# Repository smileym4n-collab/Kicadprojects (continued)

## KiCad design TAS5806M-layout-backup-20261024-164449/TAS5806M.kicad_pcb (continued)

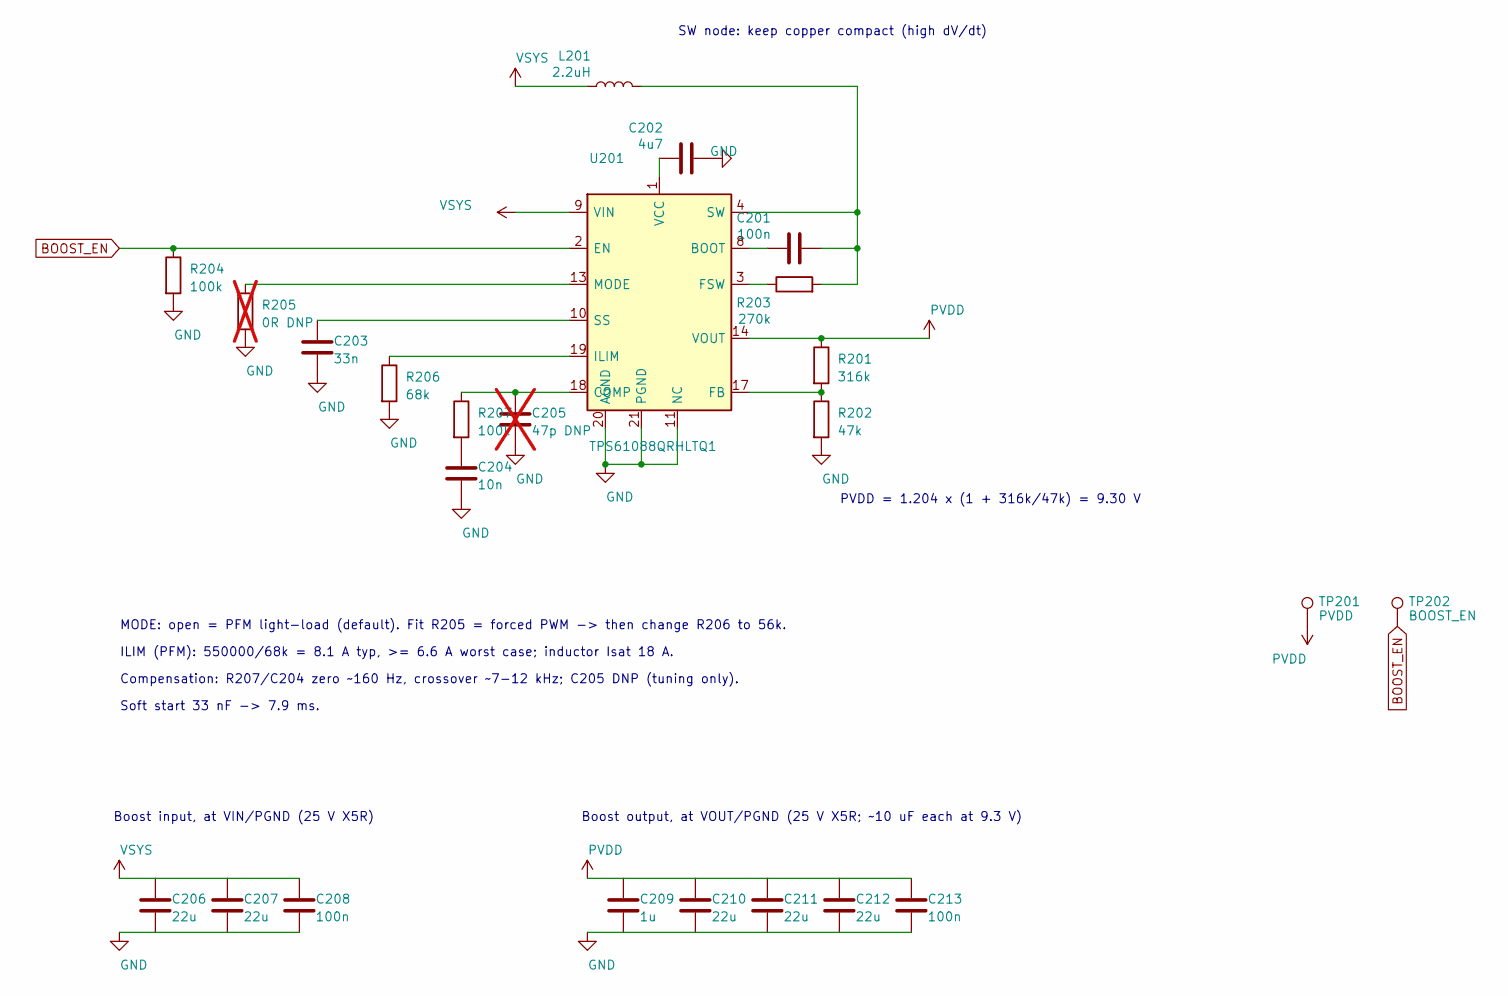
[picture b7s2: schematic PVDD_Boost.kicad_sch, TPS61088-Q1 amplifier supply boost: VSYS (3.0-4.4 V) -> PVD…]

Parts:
C201, C208, C213: 100n; C_0603_1608Metric_Pad1.08x0.95mm_HandSolder; MPN C0603C104M5RACTU
C202: 4u7; C_0805_2012Metric_Pad1.18x1.45mm_HandSolder; MPN CL21A475KAQNNNE
C203: 33n; C_0805_2012Metric_Pad1.18x1.45mm_HandSolder; MPN GRM2165C1H333JA01D
C204: 10n; C_0805_2012Metric_Pad1.18x1.45mm_HandSolder; MPN 0805N103J500CT
C205: 47p DNP; C_0603_1608Metric_Pad1.08x0.95mm_HandSolder; MPN GRM1885C1H470JA01D; not fitted
C206, C207, C210, C211, C212: 22u; C_1206_3216Metric_Pad1.33x1.80mm_HandSolder; MPN CL31A226KAHNNNE
C209: 1u; C_0805_2012Metric_Pad1.18x1.45mm_HandSolder; MPN CL21B105KAFNNNG
L201: 2.2uH; L_Bourns_SRP6060FA_BournsLayout; MPN SRP6060FA-2R2M
R201: 316k; R_0805_2012Metric; MPN 316K thick film 2012
R202: 47k; R_0805_2012Metric; MPN RMCF0805FT47K0
R203: 270k; R_0805_2012Metric; MPN 270K thick film 2012
R204: 100k; R_0805_2012Metric; MPN 100K thick film 2012
R205: 0R DNP; R_0805_2012Metric; MPN 0R link 2012; not fitted
R206: 68k; R_0805_2012Metric; MPN RC0805FR-0768KL
R207: 100k; R_0805_2012Metric; MPN 100K thin film 2012
TP201: PVDD; TestPoint_Pad_D1.5mm
TP202: BOOST_EN; TestPoint_Pad_D1.5mm
U201: TPS61088QRHLTQ1; Texas_VQFN-RHL-20_ThermalVias; MPN TPS61088QRHLTQ1

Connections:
BOOST_EN: R204.1, TP202.1 (1_1), U201.2 (EN); also elsewhere on the board
GND: C202.2, C203.2, C204.2, C205.2, C206.2, C207.2, C208.2, C209.2, C210.2, C211.2, C212.2, C213.2, R202.2, R204.2, R205.2, R206.2, U201.11 (NC), U201.12 (NC), U201.20 (AGND), U201.21 (PGND); also elsewhere on the board
unnamed: C201.2, L201.2, R203.2, U201.4 (SW), U201.5 (SW), U201.6 (SW), U201.7 (SW)
unnamed: C204.1, R207.2
unnamed: C201.1, U201.8 (BOOT)
unnamed: C205.1, R207.1, U201.18 (COMP)
unnamed: R201.2, R202.1, U201.17 (FB)
unnamed: R203.1, U201.3 (FSW)
unnamed: R206.1, U201.19 (ILIM)
unnamed: R205.1, U201.13 (MODE)
unnamed: C203.1, U201.10 (SS)
unnamed: C202.1, U201.1 (VCC)
PVDD: C209.1, C210.1, C211.1, C212.1, C213.1, R201.1, TP201.1 (1_1), U201.14 (VOUT), U201.15 (VOUT), U201.16 (VOUT); also elsewhere on the board
VSYS: C206.1, C207.1, C208.1, L201.1, U201.9 (VIN); also elsewhere on the board

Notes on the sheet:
ILIM (PFM): 550000/68k = 8.1 A typ, >= 6.6 A worst case; inductor Isat 18 A.
PVDD = 1.204 x (1 + 316k/47k) = 9.30 V
SW node: keep copper compact (high dV/dt)
MODE: open = PFM light-load (default). Fit R205 = forced PWM -> then change R206 to 56k.
Soft start 33 nF -> 7.9 ms.
Boost output, at VOUT/PGND (25 V X5R; ~10 uF each at 9.3 V)
Compensation: R207/C204 zero ~160 Hz, crossover ~7-12 kHz; C205 DNP (tuning only).
Boost input, at VIN/PGND (25 V X5R)

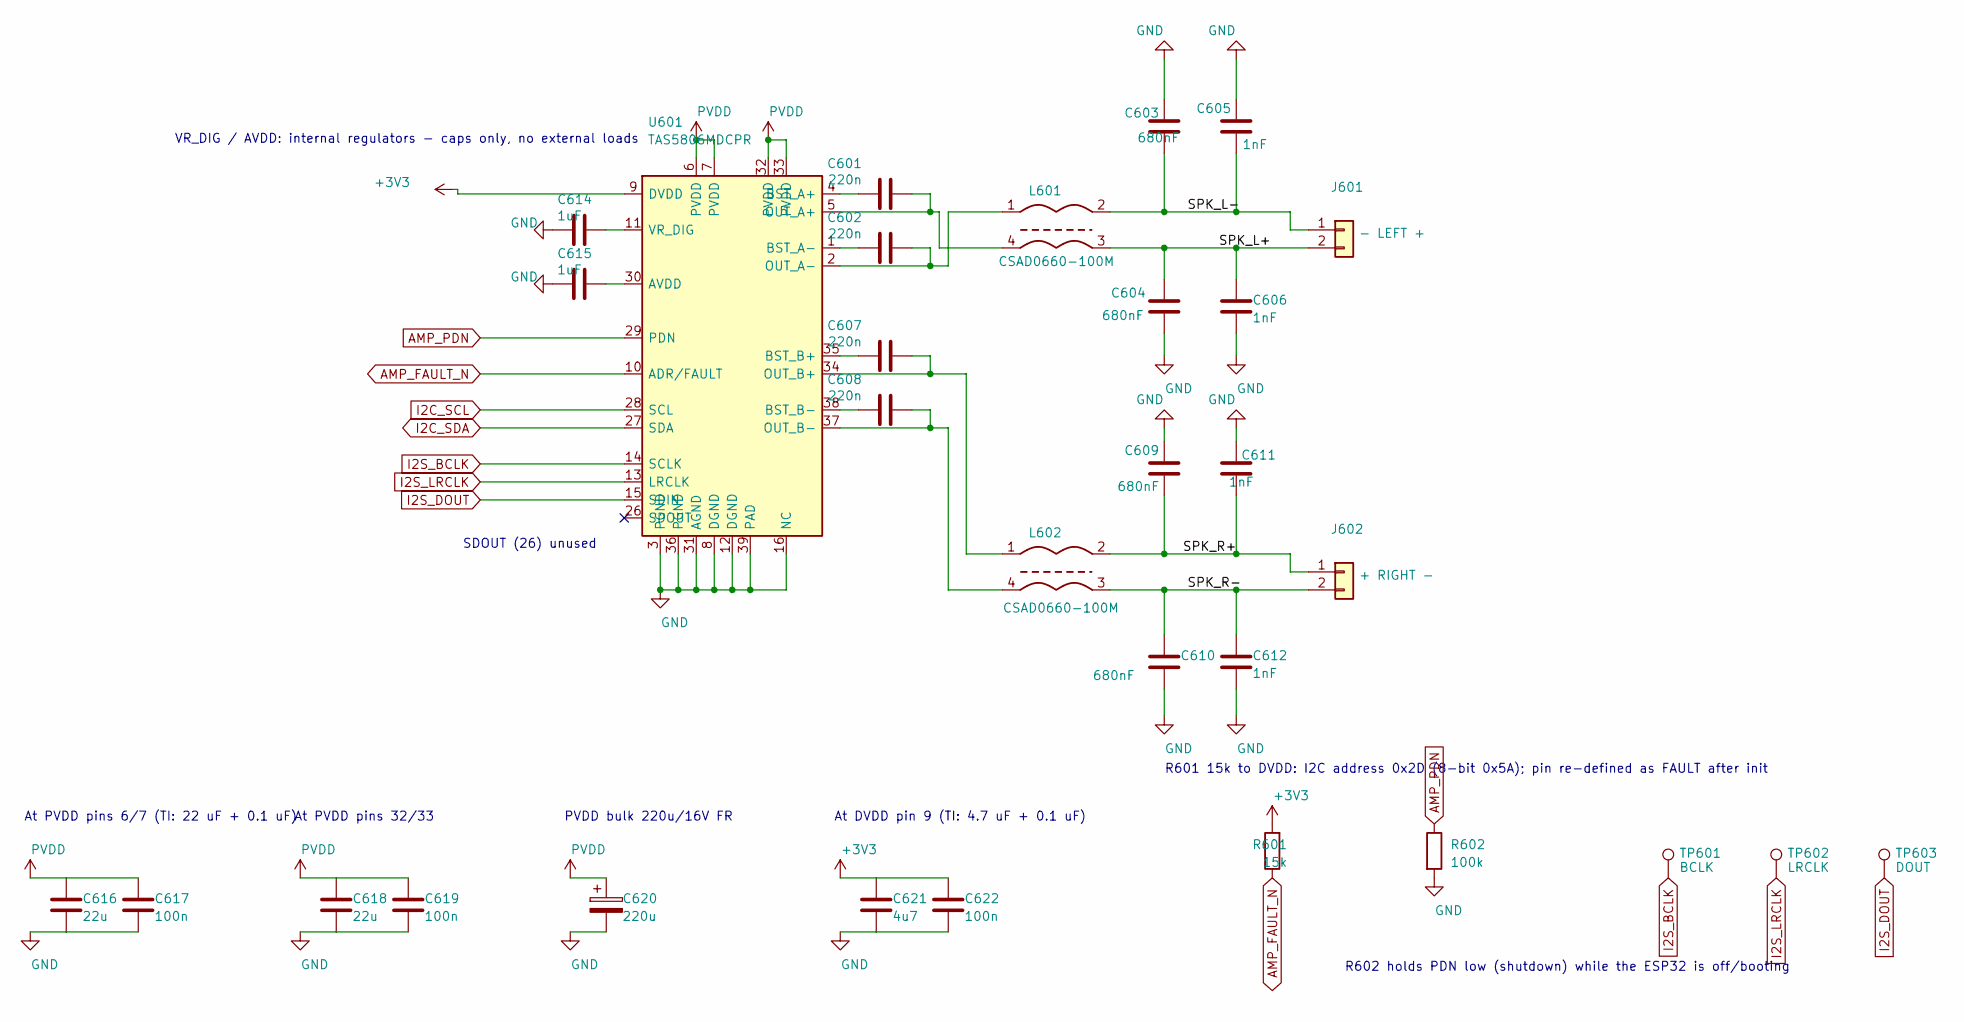
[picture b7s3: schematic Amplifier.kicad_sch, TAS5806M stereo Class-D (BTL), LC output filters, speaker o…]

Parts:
C601, C602, C607, C608: 220n; C_0805_2012Metric_Pad1.18x1.45mm_HandSolder; MPN CL21B224KAFNNNE
C603, C604, C609, C610: 680nF; C_Rect_L7.2mm_W4.5mm_P5.00mm_FKS2_FKP2_MKS2_MKP2; MPN R82DC3680Z360J
C605, C606, C611, C612: 1nF; C_0805_2012Metric_Pad1.18x1.45mm_HandSolder; MPN MC0805N102J500CT
C614, C615: 1uF; C_0805_2012Metric_Pad1.18x1.45mm_HandSolder; MPN CL21B105KAFNNNG
C616, C618: 22u; C_1206_3216Metric_Pad1.33x1.80mm_HandSolder; MPN CL31A226KAHNNNE
C617, C619, C622: 100n; C_0603_1608Metric_Pad1.08x0.95mm_HandSolder; MPN C0603C104M5RACTU
C620: 220u; CP_Radial_D6.3mm_P2.50mm; MPN EEUFR1C221B
C621: 4u7; C_0805_2012Metric_Pad1.18x1.45mm_HandSolder; MPN CL21A475KAQNNNE
J601: - LEFT +; Molex_KK-254_AE-6410-02A_1x02_P2.54mm_Vertical; MPN MC34629 (+ housing MC34481)
J602: + RIGHT -; Molex_KK-254_AE-6410-02A_1x02_P2.54mm_Vertical; MPN MC34629 (+ housing MC34481)
L601, L602: CSAD0660-100M; MPN CSAD0660-100M
R601: 15k; R_0805_2012Metric; MPN 15K thin film 2012
R602: 100k; R_0805_2012Metric; MPN 100K thick film 2012
TP601: BCLK; TestPoint_Pad_D1.5mm
TP602: LRCLK; TestPoint_Pad_D1.5mm
TP603: DOUT; TestPoint_Pad_D1.5mm
U601: TAS5806MDCPR; HTSSOP-38-1EP_4.4x9.7mm_P0.5mm_EP2.74x4.75mm_ThermalVias; MPN TAS5806MDCPR

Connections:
+3V3: C621.1, C622.1, R601.2, U601.9 (DVDD); also elsewhere on the board
/AMPLIFIER/SPK_L+: C604.1, C606.1, J601.2, L601.3
/AMPLIFIER/SPK_L-: C603.1, C605.1, J601.1, L601.2
/AMPLIFIER/SPK_R+: C609.1, C611.1, J602.1, L602.2
/AMPLIFIER/SPK_R-: C610.1, C612.1, J602.2, L602.3
AMP_FAULT_N: R601.1, U601.10 (ADR/FAULT); also elsewhere on the board
AMP_PDN: R602.1, U601.29 (PDN); also elsewhere on the board
GND: C603.2, C604.2, C605.2, C606.2, C609.2, C610.2, C611.2, C612.2, C614.2, C615.2, C616.2, C617.2, C618.2, C619.2, C620.2, C621.2, C622.2, R602.2, U601.3 (PGND), U601.8 (DGND), U601.12 (DGND), U601.16 (NC), U601.17 (NC), U601.18 (NC), U601.19 (NC), U601.20 (NC), U601.21 (NC), U601.22 (NC), U601.23 (NC), U601.24 (NC), U601.25 (NC), U601.31 (AGND), U601.36 (PGND), U601.39 (PAD); also elsewhere on the board
I2C_SCL: U601.28 (SCL); also elsewhere on the board
I2C_SDA: U601.27 (SDA); also elsewhere on the board
I2S_BCLK: TP601.1 (1_1), U601.14 (SCLK); also elsewhere on the board
I2S_DOUT: TP603.1 (1_1), U601.15 (SDIN); also elsewhere on the board
I2S_LRCLK: TP602.1 (1_1), U601.13 (LRCLK); also elsewhere on the board
unnamed: C615.1, U601.30 (AVDD)
unnamed: C601.1, U601.4 (BST_A+)
unnamed: C602.1, U601.1 (BST_A-)
unnamed: C607.1, U601.35 (BST_B+)
unnamed: C608.1, U601.38 (BST_B-)
unnamed: C601.2, L601.4, U601.5 (OUT_A+)
unnamed: C602.2, L601.1, U601.2 (OUT_A-)
unnamed: C607.2, L602.1, U601.34 (OUT_B+)
unnamed: C608.2, L602.4, U601.37 (OUT_B-)
unnamed: C614.1, U601.11 (VR_DIG)
PVDD: C616.1, C617.1, C618.1, C619.1, C620.1, U601.6 (PVDD), U601.7 (PVDD), U601.32 (PVDD), U601.33 (PVDD); also elsewhere on the board

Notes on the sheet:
R601 15k to DVDD: I2C address 0x2D (8-bit 0x5A); pin re-defined as FAULT after init
At PVDD pins 32/33
VR_DIG / AVDD: internal regulators - caps only, no external loads
PVDD bulk 220u/16V FR
At PVDD pins 6/7 (TI: 22 uF + 0.1 uF)
R602 holds PDN low (shutdown) while the ESP32 is off/booting
SDOUT (26) unused
At DVDD pin 9 (TI: 4.7 uF + 0.1 uF)

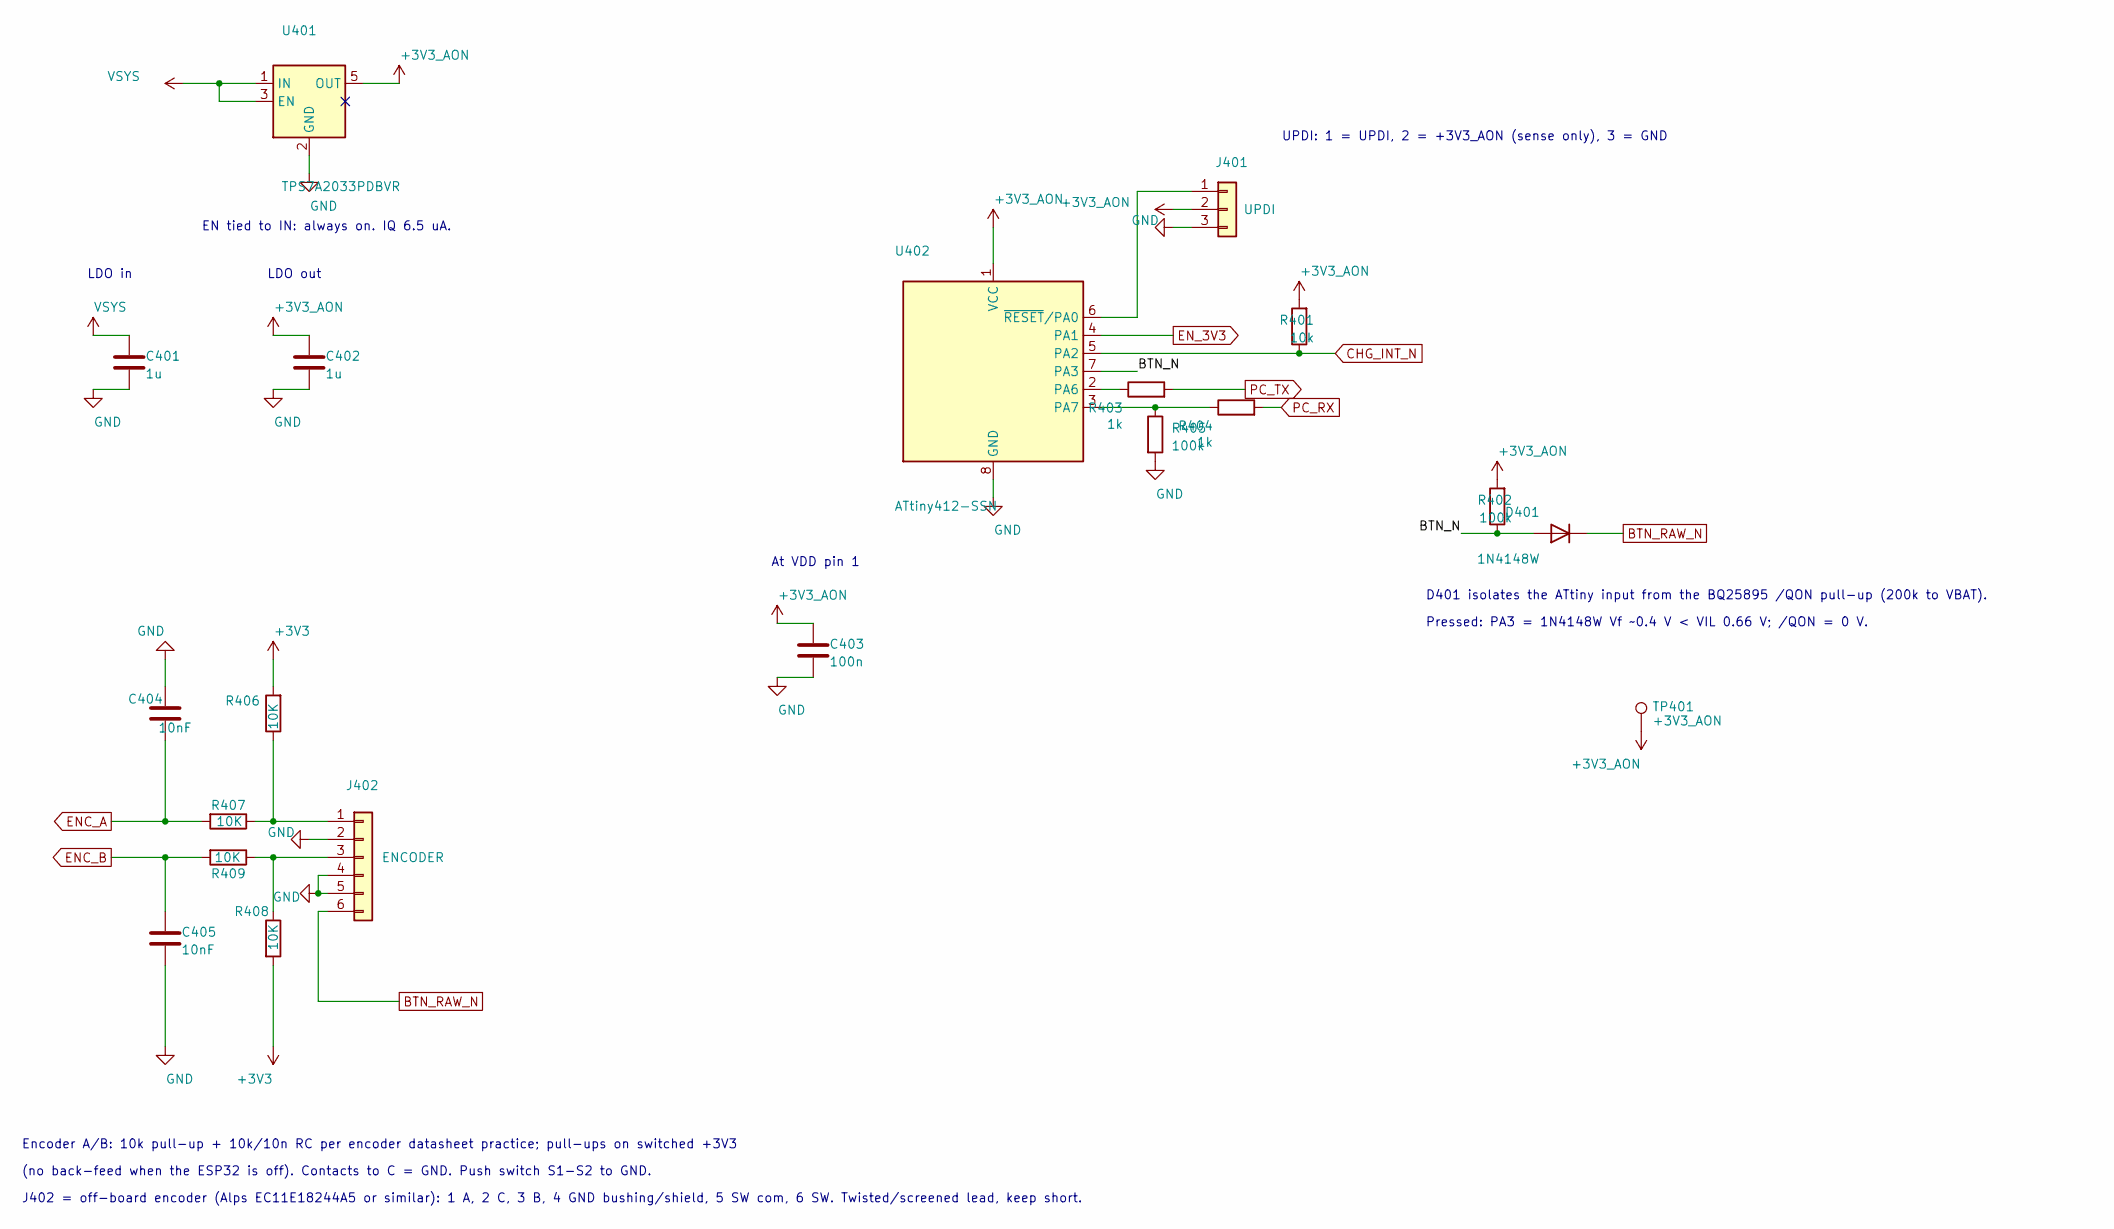
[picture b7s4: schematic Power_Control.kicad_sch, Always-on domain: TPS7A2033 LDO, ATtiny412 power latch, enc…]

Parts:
C401, C402: 1u; C_0805_2012Metric_Pad1.18x1.45mm_HandSolder; MPN CL21B105KAFNNNG
C403: 100n; C_0603_1608Metric_Pad1.08x0.95mm_HandSolder; MPN C0603C104M5RACTU
C404, C405: 10nF; C_0805_2012Metric_Pad1.18x1.45mm_HandSolder; MPN 0805N103J500CT
D401: 1N4148W; D_SOD-123; MPN 1N4148W
J401: UPDI; Molex_KK-254_AE-6410-03A_1x03_P2.54mm_Vertical; MPN MC34631 (+ housing MC34483)
J402: ENCODER; Molex_KK-254_AE-6410-06A_1x06_P2.54mm_Vertical; MPN MC34635 (+ housing MC34487)
R401: 10k; R_0805_2012Metric; MPN RK73B2ATTD103J
R402, R405: 100k; R_0805_2012Metric; MPN 100K thick film 2012
R403, R404: 1k; R_0805_2012Metric; MPN 1K thick film 2012
R406, R407, R408, R409: 10K; R_0805_2012Metric; MPN RK73B2ATTD103J
TP401: +3V3_AON; TestPoint_Pad_D1.5mm
U401: TPS7A2033PDBVR; SOT-23-5; MPN TPS7A2033PDBVR
U402: ATtiny412-SSN; SOIC-8_3.9x4.9mm_P1.27mm; MPN ATTINY412-SSN

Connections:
+3V3: R406.2, R408.2; also elsewhere on the board
+3V3_AON: C402.1, C403.1, J401.2, R401.2, R402.2, TP401.1 (1_1), U401.5 (OUT), U402.1 (VCC)
/POWER_CTRL/BTN_N: D401.2 (A), R402.1, U402.7 (PA3)
BTN_RAW_N: D401.1 (K), J402.6; also elsewhere on the board
CHG_INT_N: R401.1, U402.5 (PA2); also elsewhere on the board
ENC_A: C404.1, R407.2; also elsewhere on the board
ENC_B: C405.1, R409.2; also elsewhere on the board
EN_3V3: U402.4 (PA1); also elsewhere on the board
GND: C401.2, C402.2, C403.2, C404.2, C405.2, J401.3, J402.2, J402.4, J402.5, R405.2, U401.2 (GND), U402.8 (GND); also elsewhere on the board
unnamed: J401.1, U402.6 (~RESET/PA0)
unnamed: J402.1, R406.1, R407.1
unnamed: J402.3, R408.1, R409.1
unnamed: R403.1, U402.2 (PA6)
unnamed: R404.1, R405.1, U402.3 (PA7)
PC_RX: R404.2; also elsewhere on the board
PC_TX: R403.2; also elsewhere on the board
VSYS: C401.1, U401.1 (IN), U401.3 (EN); also elsewhere on the board

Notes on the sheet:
D401 isolates the ATtiny input from the BQ25895 /QON pull-up (200k to VBAT).
EN tied to IN: always on. IQ 6.5 uA.
Encoder A/B: 10k pull-up + 10k/10n RC per encoder datasheet practice; pull-ups on switched +3V3
UPDI: 1 = UPDI, 2 = +3V3_AON (sense only), 3 = GND
LDO in
At VDD pin 1
LDO out
J402 = off-board encoder (Alps EC11E18244A5 or similar): 1 A, 2 C, 3 B, 4 GND bushing/shield, 5 SW com, 6 SW. Twisted/screened lead, keep short.
Pressed: PA3 = 1N4148W Vf ~0.4 V < VIL 0.66 V; /QON = 0 V.
(no back-feed when the ESP32 is off). Contacts to C = GND. Push switch S1-S2 to GND.

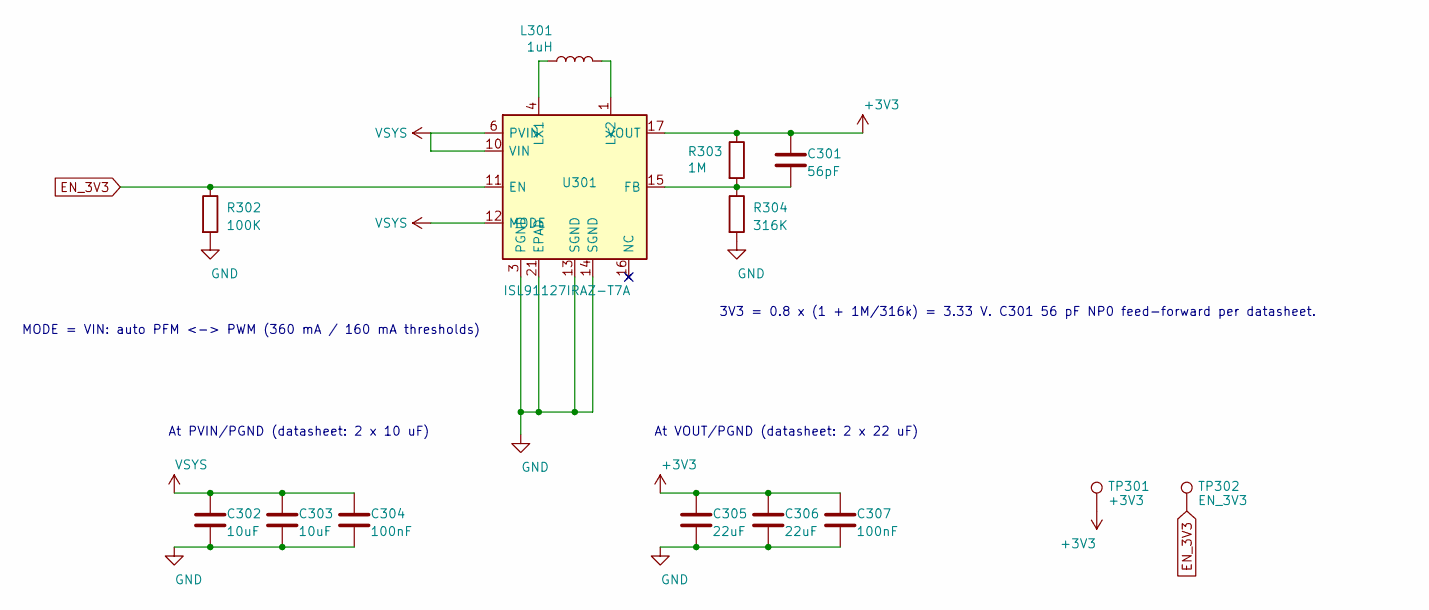
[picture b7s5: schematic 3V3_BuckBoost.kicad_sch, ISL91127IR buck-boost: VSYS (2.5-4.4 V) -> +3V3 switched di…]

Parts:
C301: 56pF; C_0603_1608Metric_Pad1.08x0.95mm_HandSolder; MPN GRM1885C1H560JA01D
C302, C303: 10uF; C_1206_3216Metric_Pad1.33x1.80mm_HandSolder; MPN TMK316B7106KL-TD
C304, C307: 100nF; C_0603_1608Metric_Pad1.08x0.95mm_HandSolder; MPN C0603C104M5RACTU
C305, C306: 22uF; C_0805_2012Metric_Pad1.18x1.45mm_HandSolder; MPN (inventory id 339, MPN not recorded)
L301: 1uH; L_Wuerth_MAPI-4020; MPN 74438356010
R302: 100K; R_0805_2012Metric; MPN 100K thick film 2012
R303: 1M; R_0805_2012Metric; MPN 1M thin film 2012
R304: 316K; R_0805_2012Metric; MPN 316K thick film 2012
TP301: +3V3; TestPoint_Pad_D1.5mm
TP302: EN_3V3; TestPoint_Pad_D1.5mm
U301: ISL91127IRAZ-T7A; QFN-20-1EP_4x4mm_P0.5mm_EP2.7x2.7mm_ThermalVias; MPN ISL91127IRAZ-T7A

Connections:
+3V3: C301.1, C305.1, C306.1, C307.1, R303.1, TP301.1 (1_1), U301.17 (VOUT), U301.18 (VOUT), U301.19 (VOUT), U301.20 (VOUT); also elsewhere on the board
EN_3V3: R302.1, TP302.1 (1_1), U301.11 (EN); also elsewhere on the board
GND: C302.2, C303.2, C304.2, C305.2, C306.2, C307.2, R302.2, R304.2, U301.3 (PGND), U301.13 (SGND), U301.14 (SGND), U301.21 (EPAD); also elsewhere on the board
unnamed: L301.1, U301.4 (LX1), U301.5 (LX1)
unnamed: L301.2, U301.1 (LX2), U301.2 (LX2)
unnamed: C301.2, R303.2, R304.1, U301.15 (FB)
VSYS: C302.1, C303.1, C304.1, U301.6 (PVIN), U301.7 (PVIN), U301.8 (PVIN), U301.9 (PVIN), U301.10 (VIN), U301.12 (MODE); also elsewhere on the board

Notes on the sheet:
At PVIN/PGND (datasheet: 2 x 10 uF)
At VOUT/PGND (datasheet: 2 x 22 uF)
MODE = VIN: auto PFM <-> PWM (360 mA / 160 mA thresholds)
3V3 = 0.8 x (1 + 1M/316k) = 3.33 V. C301 56 pF NP0 feed-forward per datasheet.

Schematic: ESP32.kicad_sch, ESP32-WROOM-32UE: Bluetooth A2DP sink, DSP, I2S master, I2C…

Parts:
C501: 1u; C_0805_2012Metric_Pad1.18x1.45mm_HandSolder; MPN CL21B105KAFNNNG
C502: 22u; C_0805_2012Metric_Pad1.18x1.45mm_HandSolder; MPN (inventory id 339, MPN not recorded)
C503: 10u; C_0805_2012Metric_Pad1.18x1.45mm_HandSolder; MPN CL21A106KOQNNNF
C504: 100n; C_0603_1608Metric_Pad1.08x0.95mm_HandSolder; MPN C0603C104M5RACTU
D501: GREEN; LED_0805_2012Metric; MPN KP-2012LSGC
J501: ESP PROG; PinHeader_1x06_P2.54mm_Vertical; MPN MC34635
R501, R506: 10k; R_0805_2012Metric; MPN RK73B2ATTD103J
R502, R503, R504: 22R; R_0603_1608Metric; MPN RK73B1JTTD220J
R505: 1k; R_0805_2012Metric; MPN 1K thick film 2012
R507, R508: 4k7; R_0805_2012Metric; MPN RMCF0805FT4K70
SW501: RESET; TS026650BK100SCRD; MPN TS02-66-50-BK-100-SCR-D
SW502: BOOT; TS026650BK100SCRD; MPN TS02-66-50-BK-100-SCR-D
TP501: IO14; TestPoint_Pad_D1.5mm
TP502: IO17; TestPoint_Pad_D1.5mm
TP503: IO19; TestPoint_Pad_D1.5mm
U501: ESP32-WROOM-32UE-N8R2; ESP32WROOM32UEN8R2; MPN ESP32-WROOM-32UE-N8R2

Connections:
+3V3: C502.1, C503.1, C504.1, J501.2, R501.2, R506.2, R507.2, R508.2, U501.2 (3V3); also elsewhere on the board
/ESP32/ESP_EN: C501.1, J501.5, R501.1, SW501.1 (NO), SW501.2 (NO), U501.3 (EN)
/ESP32/ESP_IO0: J501.6, SW502.1 (NO), SW502.2 (NO), U501.25 (IO0)
/ESP32/ESP_IO16: R506.1, U501.27 (IO16)
/ESP32/ESP_RXD0: J501.4, U501.34 (RXD0)
/ESP32/ESP_TXD0: J501.3, U501.35 (TXD0)
AMP_FAULT_N: U501.30 (IO18); also elsewhere on the board
AMP_PDN: U501.37 (IO23); also elsewhere on the board
BOOST_EN: U501.26 (IO4); also elsewhere on the board
CC1_SENSE: U501.4 (SENSOR_VP); also elsewhere on the board
CC2_SENSE: U501.5 (SENSOR_VN); also elsewhere on the board
ENC_A: U501.6 (IO34); also elsewhere on the board
ENC_B: U501.7 (IO35); also elsewhere on the board
GND: C501.2, C502.2, C503.2, C504.2, D501.1 (K), J501.1, SW501.3 (COM), SW501.4 (COM), SW502.3 (COM), SW502.4 (COM), U501.1 (GND_1), U501.15 (GND_2), U501.38 (GND_3), U501.39 (GND_4), U501.40 (GND_5), U501.41 (GND_6), U501.42 (GND_7), U501.43 (GND_8), U501.44 (GND_9), U501.45 (GND_10), U501.46 (GND_11), U501.47 (GND_12); also elsewhere on the board
I2C_SCL: R508.1, U501.36 (IO22); also elsewhere on the board
I2C_SDA: R507.1, U501.33 (IO21); also elsewhere on the board
I2S_BCLK: R503.2; also elsewhere on the board
I2S_DOUT: R504.2; also elsewhere on the board
I2S_LRCLK: R502.2; also elsewhere on the board
unnamed: D501.2 (A), R505.2
unnamed: R505.1, U501.16 (IO13)
unnamed: TP501.1 (1_1), U501.13 (IO14)
unnamed: TP502.1 (1_1), U501.28 (IO17)
unnamed: TP503.1 (1_1), U501.31 (IO19)
unnamed: R502.1, U501.10 (IO25)
unnamed: R503.1, U501.11 (IO26)
unnamed: R504.1, U501.12 (IO27)
PC_RX: U501.9 (IO33); also elsewhere on the board
PC_TX: U501.8 (IO32); also elsewhere on the board

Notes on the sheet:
disconnected (ISL91127 off: its 120R output discharge draws ~27 mA - acceptable).
ANTENNA: WROOM-32UE uses an external U.FL antenna - route the coax away from PVDD/boost/Class-D
J501: 1 GND, 2 +3V3, 3 TXD0 (ESP out), 4 RXD0 (ESP in), 5 EN, 6 IO0.
EN RC 10k / 1u per Espressif (power-up delay)
Pin 2 may power the 3V3 rail from a 3.3 V adapter for bench flashing with the battery
At module pin 2 (Espressif: 22 uF + 100 nF; +10 uF for RF bursts)
IO16 = PSRAM CS on N8R2: 10k pull-up (Espressif)
Bus is unpowered (0 V) when +3V3 is off - BQ25895 SCL/SDA tolerate this.
17-22: module NC. IO15/IO2/IO12: strapping, unused.
outputs; no PCB keep-out is required for the UE variant (datasheet sec. 3.1).
22R source terminations at the ESP32 pins (I2S lines to TAS5806M)
IO0 has an internal pull-up; hold BOOT while pulsing RESET for the ROM loader.
I2C pull-ups 4k7 to +3V3 (400 kHz, BQ25895 + TAS5806M).

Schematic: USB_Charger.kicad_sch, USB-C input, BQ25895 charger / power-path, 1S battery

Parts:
C101, C102: 10n; C_0805_2012Metric_Pad1.18x1.45mm_HandSolder; MPN 0805N103J500CT
C103: 10u; C_1206_3216Metric_Pad1.33x1.80mm_HandSolder; MPN CL31A106KBHNNNE
C104: 47n; C_0603_1608Metric_Pad1.08x0.95mm_HandSolder; MPN GRM188R71H473KA61D
C105: 1u; C_0805_2012Metric_Pad1.18x1.45mm_HandSolder; MPN CL21B105KAFNNNG
C106, C107: 22u; C_1206_3216Metric_Pad1.33x1.80mm_HandSolder; MPN CL31A226KAHNNNE
C108, C111: 100n; C_0603_1608Metric_Pad1.08x0.95mm_HandSolder; MPN C0603C104M5RACTU
C109: 10u; C_1206_3216Metric_Pad1.33x1.80mm_HandSolder; MPN TMK316B7106KL-TD
C110: 4u7; C_0805_2012Metric_Pad1.18x1.45mm_HandSolder; MPN CL21A475KAQNNNE
D101: TVS1400DRVR; WSON-6-1EP_2x2mm_P0.65mm_EP1x1.6mm; MPN TVS1400DRVR
D102: RED; LED_0805_2012Metric; MPN KP-2012EC
F101: 8A; Fuse_Littelfuse-NANO2-451_453; MPN 0451008.MRL
J101: USB4105-GF-A; USB_C_Receptacle_GCT_USB4105-xx-A_16P_TopMnt_Horizontal; MPN USB4105-GF-A
J102: BATTERY 1S; Molex_KK-396_A-41791-0002_1x02_P3.96mm_Vertical; MPN 09-65-2028 (41791-0002)
J103: BATT NTC 10k; Molex_KK-254_AE-6410-02A_1x02_P2.54mm_Vertical; MPN MC34629 (+ housing MC34481)
L101: 1uH; L_Wuerth_MAPI-4020; MPN 74438356010
R101: 150R; R_0805_2012Metric; MPN RC0805FR-07150RL
R102, R104: 5K1; R_0805_2012Metric; MPN RC0805FR-135K1L
R103, R105: 100k; R_0805_2012Metric; MPN 100K thick film 2012
R106: 1k5; R_0603_1608Metric; MPN 1K5 thick film 1608
R107: 5k23; R_0805_2012Metric; MPN RMCF0805FT5K23
R108: 30k; R_0805_2012Metric; MPN RMCF0805FT30K0
RT101: 10k B3435 DNP; R_0603_1608Metric; MPN NCU18XH103F60RB; not fitted
TP101: VBUS; TestPoint_Pad_D1.5mm
TP102: VSYS; TestPoint_Pad_D1.5mm
TP103: VBAT; TestPoint_Pad_D1.5mm
TP104: GND; TestPoint_Pad_D1.5mm
U101: BQ25895RTWR; Texas_RTW_WQFN-24-1EP_4x4mm_P0.5mm_EP2.7x2.7mm_ThermalVias; MPN BQ25895RTWR
U102: TPD2E2U06DCKR; SOT-323_SC-70; MPN TPD2E2U06DCKR

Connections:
/USB_CHARGER/CC1: J101.A5 (CC1), R102.1, R103.1
/USB_CHARGER/CC2: J101.B5 (CC2), R104.1, R105.1
/USB_CHARGER/USB_DN: J101.A7 (D-), J101.B7 (D-), U101.3 (D-), U102.2 (IO2)
/USB_CHARGER/USB_DP: J101.A6 (D+), J101.B6 (D+), U101.2 (D+), U102.1 (IO1)
BTN_RAW_N: U101.12 (~QON); also elsewhere on the board
CC1_SENSE: C101.1, R103.2; also elsewhere on the board
CC2_SENSE: C102.1, R105.2; also elsewhere on the board
CHG_INT_N: U101.7 (~INT); also elsewhere on the board
GND: C101.2, C102.2, C103.2, C105.2, C106.2, C107.2, C108.2, C109.2, C110.2, C111.2, D101.1 (GND), D101.2 (GND), D101.3 (GND), D101.7 (GND), J101.A1 (GND), J101.A12 (GND), J101.B1 (GND), J101.B12 (GND), J101.SH (SHIELD), J102.2, J103.2, R101.2, R102.2, R104.2, R108.2, RT101.2, TP104.1 (1_1), U101.8 (OTG), U101.9 (~CE), U101.17 (PGND), U101.18 (PGND), U101.25 (PGND), U102.3 (GND); also elsewhere on the board
I2C_SCL: U101.5 (SCL); also elsewhere on the board
I2C_SDA: U101.6 (SDA); also elsewhere on the board
unnamed: C104.1, L101.1, U101.19 (SW), U101.20 (SW)
unnamed: D102.2 (A), R106.1
unnamed: D102.1 (K), U101.4 (STAT)
unnamed: F101.1, J102.1
unnamed: J103.1, R107.2, R108.1, RT101.1, U101.11 (TS)
unnamed: C104.2, U101.21 (BTST)
unnamed: R101.1, U101.10 (ILIM)
unnamed: C103.1, U101.23 (PMID)
unnamed: C110.1, R107.1, U101.22 (REGN)
VBAT: C109.1, C111.1, F101.2, TP103.1 (1_1), U101.13 (BAT), U101.14 (BAT)
VBUS: C105.1, D101.4 (IN), D101.5 (IN), D101.6 (IN), J101.A4 (VBUS), J101.A9 (VBUS), J101.B4 (VBUS), J101.B9 (VBUS), TP101.1 (1_1), U101.1 (VBUS)
VSYS: C106.1, C107.1, C108.1, L101.2, R106.2, TP102.1 (1_1), U101.15 (SYS), U101.16 (SYS); also elsewhere on the board

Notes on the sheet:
Back-feed into unpowered ESP32 <= 15 uA (accepted).
CC sense: 100k series + 10n reservoir at ESP32 ADC1 (place C at ESP32).
At SYS pins 15/16 (>= 20 uF eff.)
OTG pin = GND: boost (OTG) mode can never start
Cell has internal protection (OV/UV/OC); F101 8 A and BQ25895 9 A BATFET OCP back it up.
18.4 V clamp < 22 V BQ25895 VBUS abs max
TVS1400: 14 V standoff (allows HVDCP 9/12 V),
No NTC fitted -> TS reads 85% REGN = COLD -> charging suspended (safe default).
BATTERY: pin 1 = BAT+ (red), pin 2 = BAT- (black). Polarised KK-396.
USB-C sink: Rd = 5.1k on CC1/CC2 (no PD). Shell tied to GND.
CHARGE LED: on = charging, 1 Hz blink = fault
D+/D- go only to BQ25895 BC1.2 detection.
At VBUS pin 1
NTC: 10k B3435 (103AT) bonded to the cell on J103, OR fit RT101 on board - never both.
No reverse-polarity FET fitted (see design notes): CHECK POLARITY BEFORE MATING.
At BAT pins 13/14
ILIM 150R: USB input ceiling 2.37 A typ

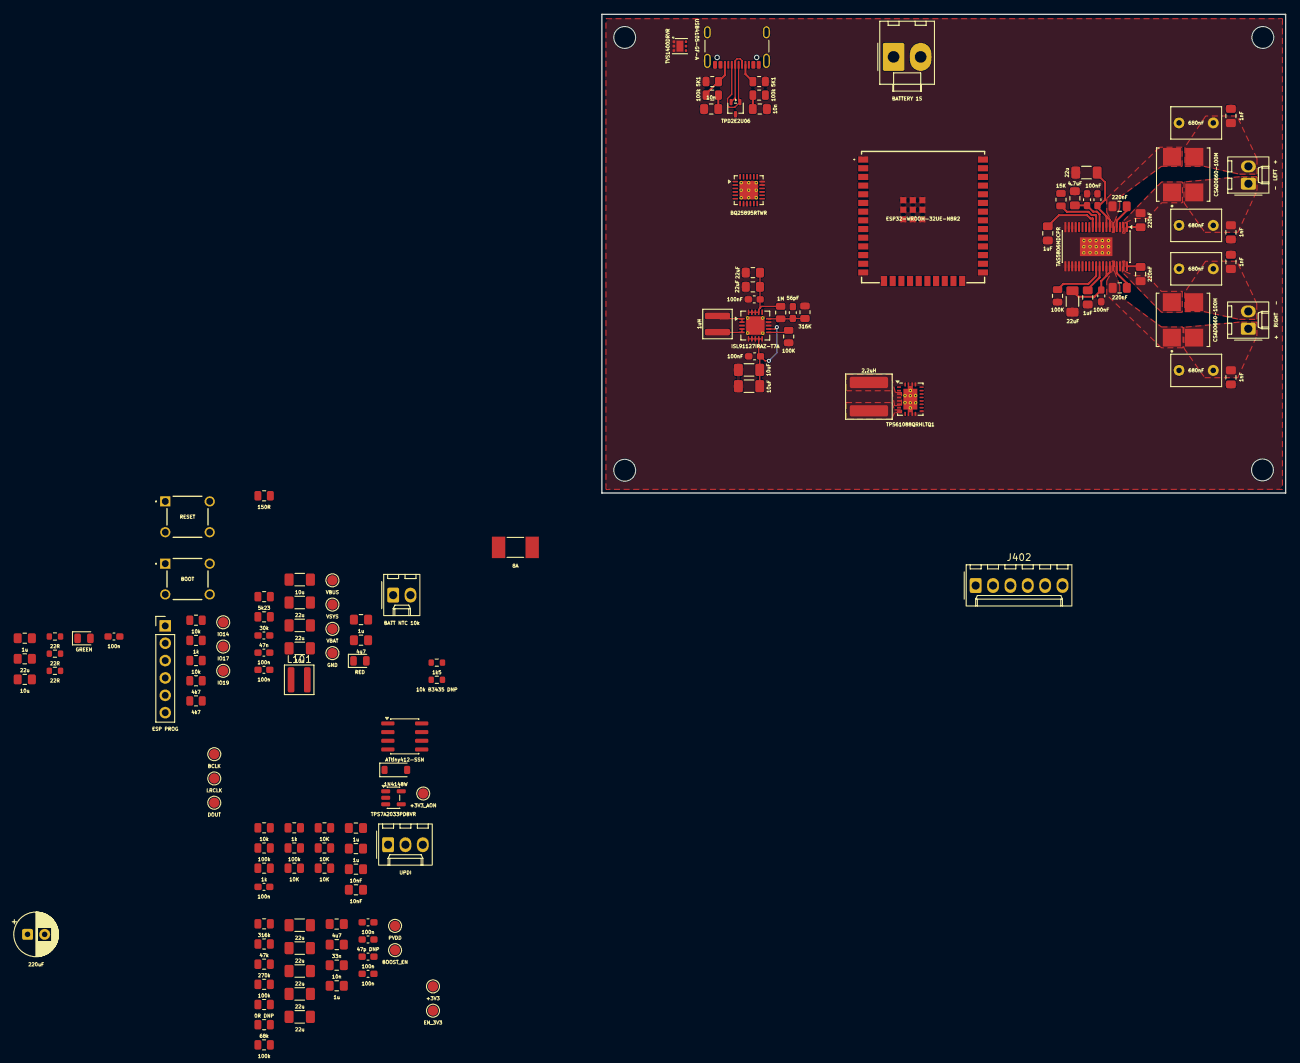
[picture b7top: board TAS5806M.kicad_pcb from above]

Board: 4 copper layers, 100.0 x 70.0 mm, 146 parts (0 on the bottom side), 83 nets.

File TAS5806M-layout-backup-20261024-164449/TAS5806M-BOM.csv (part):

"Refs","Value","Footprint","Manufacturer","MPN","Stock","Note","Qty","DNP"
"C101,C102,C204","10n","Capacitor_SMD:C_0805_2012Metric_Pad1.18x1.45mm_HandSolder","Walsin","0805N103J500CT","Inventory id 88 (qty 38)","50 V NP0","3",""
"C103","10u","Capacitor_SMD:C_1206_3216Metric_Pad1.33x1.80mm_HandSolder","Samsung","CL31A106KBHNNNE","Inventory id 505 (qty 10)","50 V X5R","1",""
"C104","47n","Capacitor_SMD:C_0603_1608Metric_Pad1.08x0.95mm_HandSolder","Murata","GRM188R71H473KA61D","Purchase","50 V X7R (BTST)","1",""
"C105,C209,C401,C402,C501","1u","Capacitor_SMD:C_0805_2012Metric_Pad1.18x1.45mm_HandSolder","Samsung","CL21B105KAFNNNG","Purchase (user standard 2012; inventory 3216 CL31B105KBHNFNE x50 fallback)","25 V X7R","5",""
"C106,C107,C206,C207,C210-C212,C616,C618","22u","Capacitor_SMD:C_1206_3216Metric_Pad1.33x1.80mm_HandSolder","Samsung","CL31A226KAHNNNE","Inventory id 202 (qty 19)","25 V X5R","9",""
"C108,C111,C201,C208,C213,C403,C504,C617,C619,C622","100n","Capacitor_SMD:C_0603_1608Metric_Pad1.08x0.95mm_HandSolder","KEMET","C0603C104M5RACTU","Purchase (user standard 1608; inventory has 3216 C1206C104K5RACTU x129 as fallback)","50 V X7R","10",""
"C109","10u","Capacitor_SMD:C_1206_3216Metric_Pad1.33x1.80mm_HandSolder","Taiyo Yuden","TMK316B7106KL-TD","Inventory id 135 (qty 50)","25 V X7R","1",""
"C110,C202,C621","4u7","Capacitor_SMD:C_0805_2012Metric_Pad1.18x1.45mm_HandSolder","Samsung","CL21A475KAQNNNE","Inventory id 133 (qty 50)","25 V X5R","3",""
"C203","33n","Capacitor_SMD:C_0805_2012Metric_Pad1.18x1.45mm_HandSolder","Murata","GRM2165C1H333JA01D","Inventory id 567 (qty 20)","50 V C0G","1",""
"C205","47p DNP","Capacitor_SMD:C_0603_1608Metric_Pad1.08x0.95mm_HandSolder","Murata","GRM1885C1H470JA01D","DNP - DNP (tuning footprint)","50 V C0G","1","DNP"
"C301","56pF","Capacitor_SMD:C_0603_1608Metric_Pad1.08x0.95mm_HandSolder","Murata","GRM1885C1H560JA01D","Purchase","50 V C0G","1",""
"C302,C303","10uF","Capacitor_SMD:C_1206_3216Metric_Pad1.33x1.80mm_HandSolder","Taiyo Yuden","TMK316B7106KL-TD","Inventory id 135 (qty 50)","25 V X7R","2",""
"C304,C307","100nF","Capacitor_SMD:C_0603_1608Metric_Pad1.08x0.95mm_HandSolder","KEMET","C0603C104M5RACTU","Purchase (user standard 1608; inventory has 3216 C1206C104K5RACTU x129 as fallback)","50 V X7R","2",""
"C305,C306","22uF","Capacitor_SMD:C_0805_2012Metric_Pad1.18x1.45mm_HandSolder","Murata","(inventory id 339, MPN not recorded)","Inventory id 339 (qty 39)","10 V X5R","2",""
"C404,C405","10nF","Capacitor_SMD:C_0805_2012Metric_Pad1.18x1.45mm_HandSolder","Walsin","0805N103J500CT","Inventory id 88 (qty 38)","50 V NP0","2",""
"C502","22u","Capacitor_SMD:C_0805_2012Metric_Pad1.18x1.45mm_HandSolder","Murata","(inventory id 339, MPN not recorded)","Inventory id 339 (qty 39)","10 V X5R","1",""
"C503","10u","Capacitor_SMD:C_0805_2012Metric_Pad1.18x1.45mm_HandSolder","Samsung","CL21A106KOQNNNF","Inventory id 184 (qty 32)","16 V X5R","1",""
"C601,C602,C607,C608","220n","Capacitor_SMD:C_0805_2012Metric_Pad1.18x1.45mm_HandSolder","Samsung","CL21B224KAFNNNE","Inventory id 84 (qty 48)","25 V X7R","4",""
"C603,C604,C609,C610","680nF","Capacitor_THT:C_Rect_L7.2mm_W4.5mm_P5.00mm_FKS2_FKP2_MKS2_MKP2","KEMET","R82DC3680Z360J","Purchase - CPC (in stock per user)","63 VDC metallised PET film, 5%, 5 mm pitch, 7.2x4.5x9.5 mm; mount flush, short GND via","4",""
"C605,C606,C611,C612","1nF","Capacitor_SMD:C_0805_2012Metric_Pad1.18x1.45mm_HandSolder","Multicomp Pro","MC0805N102J500CT","Inventory id 558 (qty 100)","50 V C0G","4",""
"C614,C615","1uF","Capacitor_SMD:C_0805_2012Metric_Pad1.18x1.45mm_HandSolder","Samsung","CL21B105KAFNNNG","Purchase (user standard 2012; inventory 3216 CL31B105KBHNFNE x50 fallback)","25 V X7R","2",""
"C620","220u","Capacitor_THT:CP_Radial_D6.3mm_P2.50mm","Panasonic","EEUFR1C221B","Inventory id 581 (qty 10)","16 V FR series low-ESR; confirm 6.3 mm body","1",""
"D101","TVS1400DRVR","Package_SON:WSON-6-1EP_2x2mm_P0.65mm_EP1x1.6mm","Texas Instruments","TVS1400DRVR","Purchase","","1",""
"D102","RED","LED_SMD:LED_0805_2012Metric","Kingbright","KP-2012EC","Inventory id 640 (qty 10)","","1",""
"D401","1N4148W","Diode_SMD:D_SOD-123","onsemi","1N4148W","Inventory id 510 (qty 67)","","1",""
"D501","GREEN","LED_SMD:LED_0805_2012Metric","Kingbright","KP-2012LSGC","Inventory id 639 (qty 1)","2 mA low-current type","1",""
"F101","8A","Fuse:Fuse_Littelfuse-NANO2-451_453","Littelfuse","0451008.MRL","Purchase","8 A very fast, 7.7 mOhm, 125 V","1",""
"J101","USB4105-GF-A","Connector_USB:USB_C_Receptacle_GCT_USB4105-xx-A_16P_TopMnt_Horizontal","GCT","USB4105-GF-A","Purchase","5 A rated USB 2.0 Type-C receptacle","1",""
"J102","BATTERY 1S","Connector_Molex:Molex_KK-396_A-41791-0002_1x02_P3.96mm_Vertical","Molex","09-65-2028 (41791-0002)","Inventory id 722 (qty 16)","KK-396 friction-lock, polarised; pin 1 = BAT+","1",""
"J103","BATT NTC 10k","Connector_Molex:Molex_KK-254_AE-6410-02A_1x02_P2.54mm_Vertical","Multicomp Pro","MC34629 (+ housing MC34481)","Inventory id 126 (qty 40)","2.54 mm friction-lock header; verify footprint vs MC34629 drawing","1",""
"J401","UPDI","Connector_Molex:Molex_KK-254_AE-6410-03A_1x03_P2.54mm_Vertical","Multicomp Pro","MC34631 (+ housing MC34483)","Inventory id 127 (qty 40)","","1",""
"J402","ENCODER","Connector_Molex:Molex_KK-254_AE-6410-06A_1x06_P2.54mm_Vertical","Multicomp Pro","MC34635 (+ housing MC34487)","Inventory id 691 (qty 10); housing id 130 (qty 10)","Remote encoder Alps EC11E18244A5 on its own panel board/flying leads; keep cable short and twisted","1",""
"J501","ESP PROG","Connector_PinHeader_2.54mm:PinHeader_1x06_P2.54mm_Vertical","Multicomp Pro","MC34635","Inventory id 691 (qty 10)","","1",""
"J601","-  LEFT  +","Connector_Molex:Molex_KK-254_AE-6410-02A_1x02_P2.54mm_Vertical","Multicomp Pro","MC34629 (+ housing MC34481)","Inventory id 126 (qty 40)","2.54 mm friction-lock header; verify footprint vs MC34629 drawing","1",""
"J602","+   RIGHT   -","Connector_Molex:Molex_KK-254_AE-6410-02A_1x02_P2.54mm_Vertical","Multicomp Pro","MC34629 (+ housing MC34481)","Inventory id 126 (qty 40)","2.54 mm friction-lock header; verify footprint vs MC34629 drawing","1",""
"L101,L301","1uH","Inductor_SMD:L_Wuerth_MAPI-4020","Würth Elektronik","74438356010","Purchase (DigiKey/Mouser/Farnell)","WE-MAPI 4020: 1.0 uH +/-20%, Isat 5.3 A (10%) / 11.5 A (30%), DCR 12 typ / 15 max mOhm, IR 10.1 A (40 K), AEC-Q200; datasheet rev 003.002, land pattern 1 = KiCad L_Wuerth_MAPI-4020","2",""
"L201","2.2uH","Soundbar:L_Bourns_SRP6060FA_BournsLayout","Bourns","SRP6060FA-2R2M","Purchase (DigiKey/Mouser/Farnell)","2.2 uH +/-20%, DCR 7.0 typ / 7.8 max mOhm, Isat 14 A (30% drop), Irms 11 A (20 C) / 14 A (40 C), 6.6 x 6.4 x 5.8 mm, AEC-Q200","1",""
"L601,L602","CSAD0660-100M","Soundbar:CSAD0660-100M","Codaca","CSAD0660-100M","Inventory id 520 (qty 2)","2 x 10 uH, DCR 47 mOhm typ, Isat 6.5 A, Irms 3.5 A","2",""
"R101","150R","Resistor_SMD:R_0805_2012Metric","Yageo","RC0805FR-07150RL","Purchase (stock 150R id 211 has no recorded tolerance)","1%; sets BQ25895 ILIM ceiling","1",""
"R102,R104","5K1","Resistor_SMD:R_0805_2012Metric","Yageo","RC0805FR-135K1L","Inventory id 374 (qty 100)","1% thick film","2",""
"R103,R105,R204,R402,R405,R602","100k","Resistor_SMD:R_0805_2012Metric","(unknown)","100K thick film 2012","Inventory id 241 (qty 77)","5% thick film","6",""
"R106","1k5","Resistor_SMD:R_0603_1608Metric","(unknown)","1K5 thick film 1608","Inventory id 226 (qty 65)","1% thick film","1",""
"R107","5k23","Resistor_SMD:R_0805_2012Metric","Stackpole","RMCF0805FT5K23","Inventory id 568 (qty 100)","1% thick film","1",""
"R108","30k","Resistor_SMD:R_0805_2012Metric","Stackpole","RMCF0805FT30K0","Inventory id 573 (qty 100)","1% thick film","1",""
"R201","316k","Resistor_SMD:R_0805_2012Metric","(unknown)","316K thick film 2012","Inventory id 245 (qty 49)","1% thick film","1",""
"R202","47k","Resistor_SMD:R_0805_2012Metric","Stackpole","RMCF0805FT47K0","Inventory id 504 (qty 100)","1% thick film","1",""
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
